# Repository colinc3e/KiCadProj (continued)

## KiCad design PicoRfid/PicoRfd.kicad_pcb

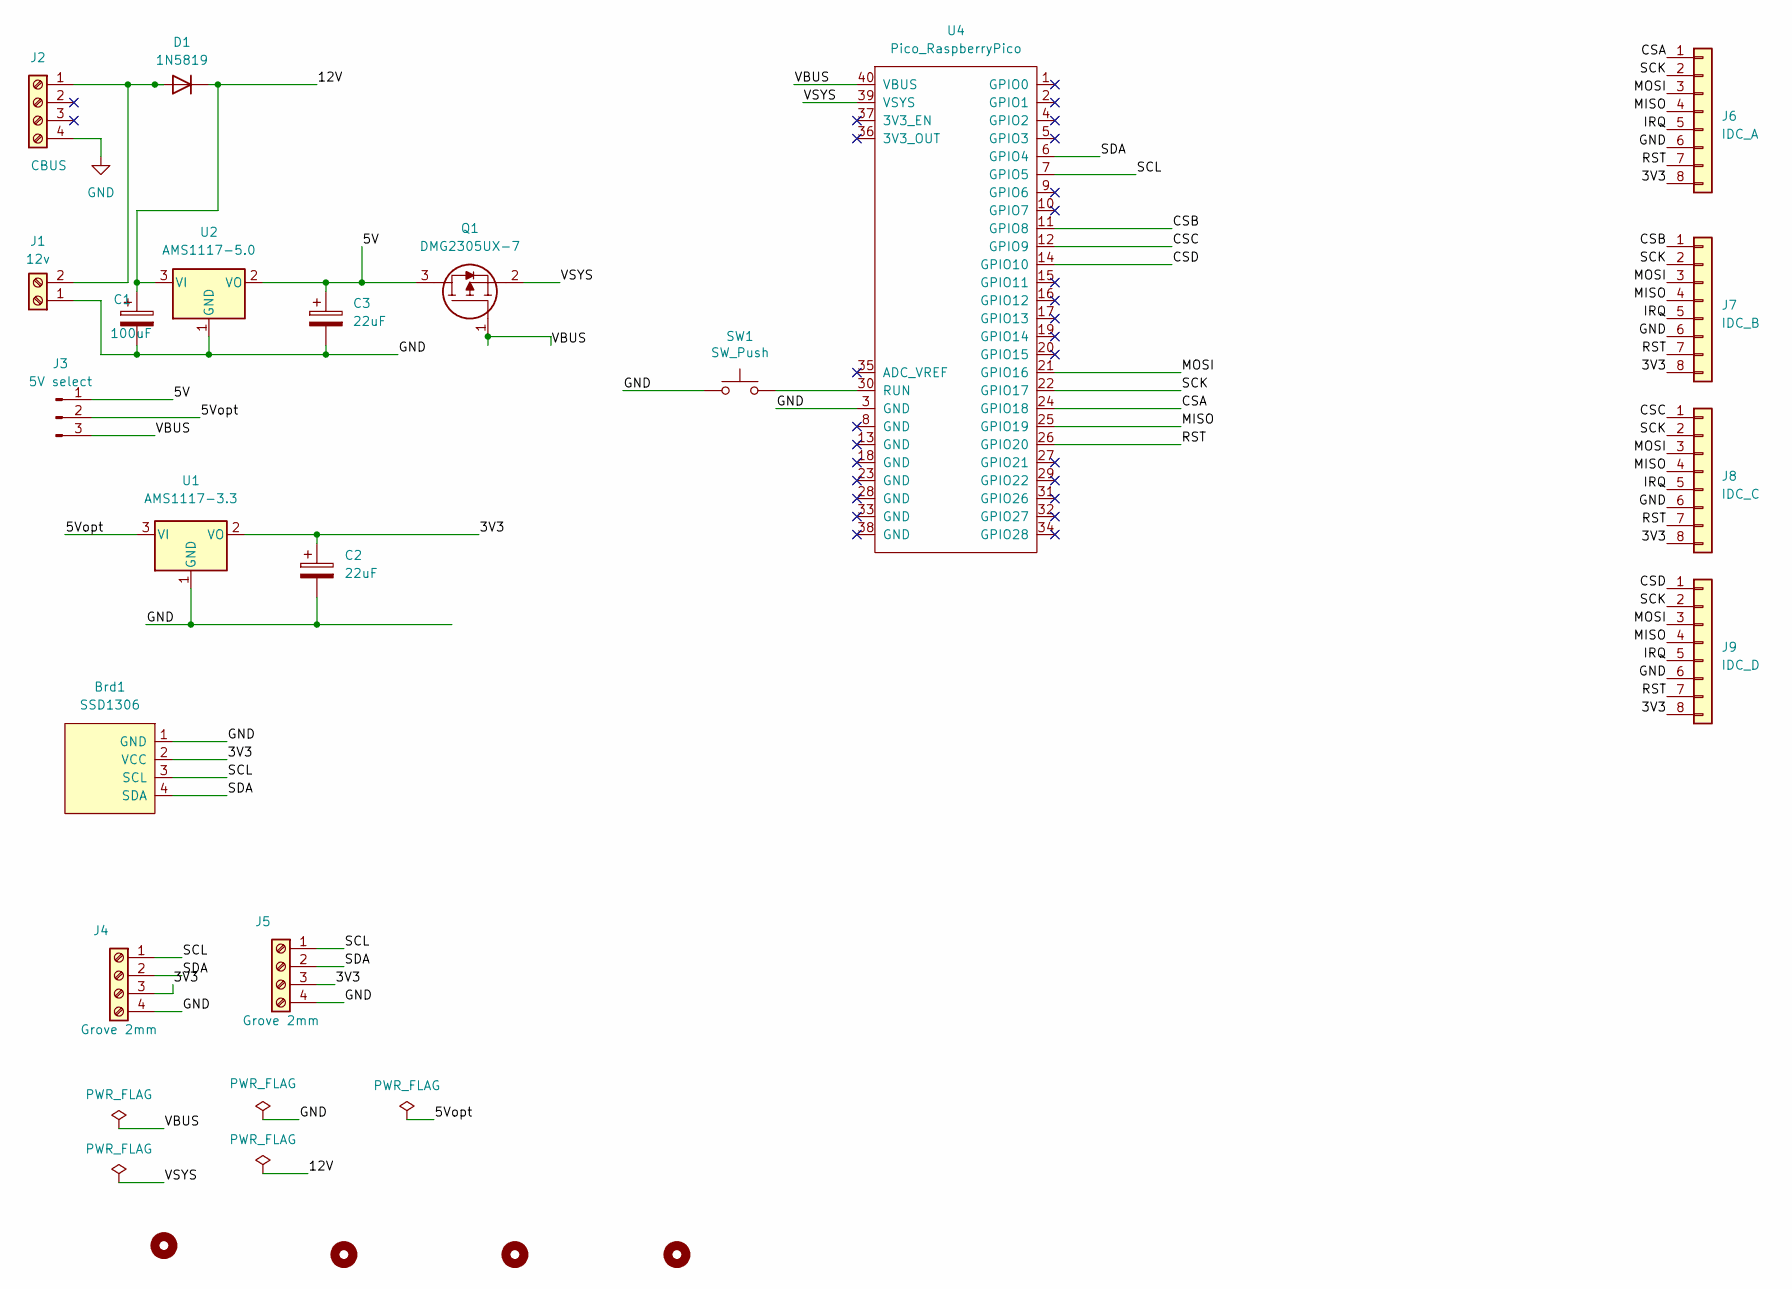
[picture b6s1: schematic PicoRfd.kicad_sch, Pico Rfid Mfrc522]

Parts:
Brd1: SSD1306; 128x64OLED
C1: 100uF; CP_Radial_D10.0mm_P7.50mm
C2, C3: 22uF; CP_Radial_Tantal_D7.0mm_P5.00mm
D1: 1N5819; D_DO-41_SOD81_P10.16mm_Horizontal
H1, H2, H3, H4: MountingHole; MountingHole_3.2mm_M3
J1: 12v; TerminalBlock_Phoenix_PT-1,5-2-3.5-H_1x02_P3.50mm_Horizontal
J2: CBUS; TerminalBlock_Phoenix_PT-1,5-4-3.5-H_1x04_P3.50mm_Horizontal
J3: 5V select; PinHeader_1x03_P2.54mm_Vertical
J4, J5: Grove 2mm; HW4-2.0
J6: IDC_A; IDC-Header_2x04_P2.54mm_Vertical
J7: IDC_B; IDC-Header_2x04_P2.54mm_Vertical
J8: IDC_C; IDC-Header_2x04_P2.54mm_Vertical
J9: IDC_D; IDC-Header_2x04_P2.54mm_Vertical
Q1: DMG2305UX-7; SOT-23-3; Mouser Part Number 621-DMG2305UX-7
SW1: SW_Push; SW_Tactile_SPST_NO_Straight_CK_PTS636Sx25SMTRLFS
U1: AMS1117-3.3; SOT-223-3_TabPin2
U2: AMS1117-5.0; SOT-223-3_TabPin2
U4: Pico_RaspberryPico; RaspberryPico_TH_NoSWD

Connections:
/3V3: Brd1.2 (VCC), C2.1, J4.3, J5.3, J6.8, J7.8, J8.8, J9.8, U1.2 (VO)
/5V: C3.1, J3.1, Q1.3, U2.2 (VO)
/5Vopt: J3.2, U1.3 (VI)
/12V: C1.1, D1.1 (K), U2.3 (VI)
/CSA: J6.1, U4.24 (GPIO18)
/CSB: J7.1, U4.11 (GPIO8)
/CSC: J8.1, U4.12 (GPIO9)
/CSD: J9.1, U4.14 (GPIO10)
/IRQ: J6.5, J7.5, J8.5, J9.5
/MISO: J6.4, J7.4, J8.4, J9.4, U4.25 (GPIO19)
/MOSI: J6.3, J7.3, J8.3, J9.3, U4.21 (GPIO16)
/RST: J6.7, J7.7, J8.7, J9.7, U4.26 (GPIO20)
/SCK: J6.2, J7.2, J8.2, J9.2, U4.22 (GPIO17)
/SCL: Brd1.3 (SCL), J4.1, J5.1, U4.7 (GPIO5)
/SDA: Brd1.4 (SDA), J4.2, J5.2, U4.6 (GPIO4)
/VBUS: J3.3, Q1.1, U4.40 (VBUS)
/VSYS: Q1.2, U4.39 (VSYS)
GND: Brd1.1 (GND), C1.2, C2.2, C3.2, J1.1, J2.4, J4.4, J5.4, J6.6, J7.6, J8.6, J9.6, SW1.1, U1.1 (GND), U2.1 (GND), U4.3 (GND)
unnamed: D1.2 (A), J1.2, J2.1
unnamed: SW1.2, U4.30 (RUN)

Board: 2 copper layers, 23 parts (0 on the bottom side), 20 nets, no tracks yet.

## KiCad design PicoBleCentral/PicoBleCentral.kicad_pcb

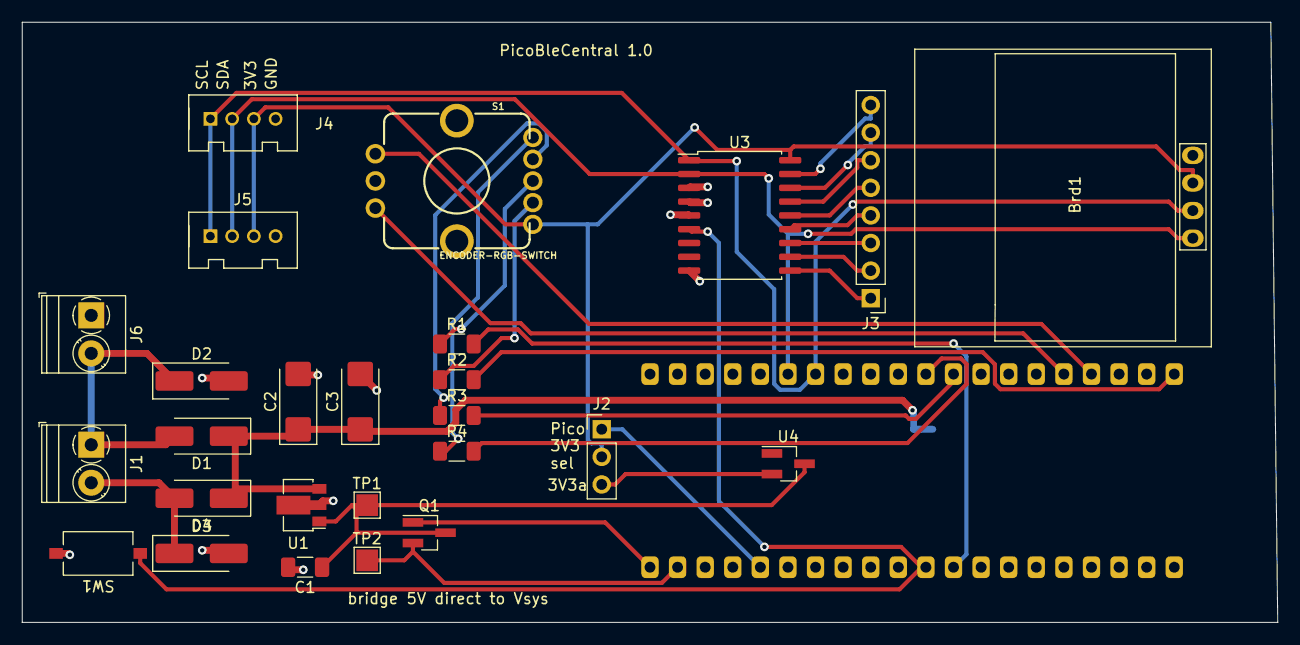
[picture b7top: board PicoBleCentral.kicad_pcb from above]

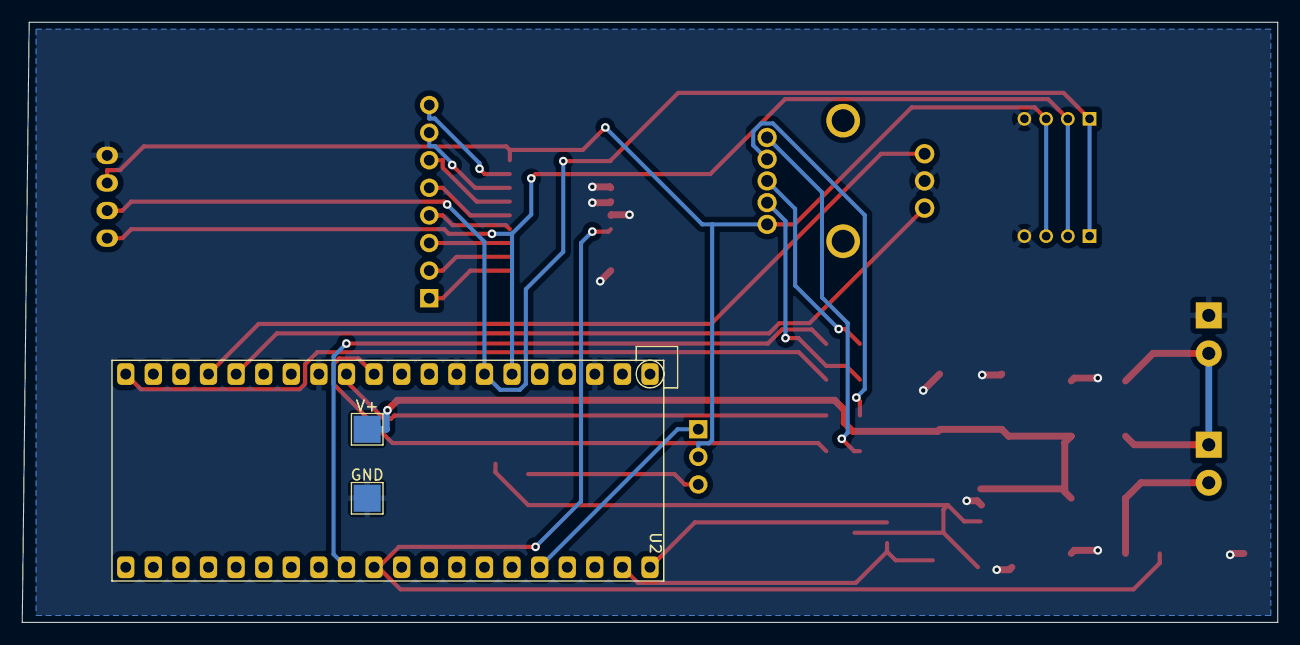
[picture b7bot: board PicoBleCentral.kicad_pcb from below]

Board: 2 copper layers, 115.6 x 55.2 mm, 29 parts (3 on the bottom side), 31 nets.

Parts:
Brd1: SSD1306; 128x64OLED
C1: 10uf/16V; C_1206_3216Metric_Pad1.33x1.80mm_HandSolder
C2: 10uF/25V; CP_EIA-6032-20_AVX-F_Pad2.25x2.35mm_HandSolder
C3: 10uF/25v; CP_EIA-6032-20_AVX-F_Pad2.25x2.35mm_HandSolder
D1, D2, D3, D4: RBR3L60AD; D_SMA_Handsoldering
GND: GND; TestPoint_Pad_2.5x2.5mm
J1: DCC; TerminalBlock_Phoenix_PT-1,5-2-3.5-H_1x02_P3.50mm_Horizontal
J2: 3V3 Sel; PinHeader_1x03_P2.54mm_Vertical
J3: keypad; PinHeader_1x08_P2.54mm_Vertical
J4: grove 2mm; HW4-2.0
J5: i2c; HW4-2.0
J6: 12V; TerminalBlock_Phoenix_PT-1,5-2-3.5-H_1x02_P3.50mm_Horizontal
Q1: DMG2305UX-7; SOT-23_Handsoldering
R1: 10k; R_1206_3216Metric_Pad1.30x1.75mm_HandSolder
R2, R3, R4: 330; R_1206_3216Metric_Pad1.30x1.75mm_HandSolder
S1: ENCODER-RGB-SWITCH; ENCODER_LED_3
SW1: SW_Push; SW_Tactile_SPST_NO_Straight_CK_PTS636Sx25SMTRLFS
TP1, TP2: TestPoint; TestPoint_Pad_2.0x2.0mm
U1: AP7384-50Y; SOT-89-3
U2: Pico_RaspberryPico; RaspberryPico_TH_NoSWD
U3: MCP23008-xSO; SOIC-18W_7.5x11.6mm_P1.27mm
U4: AMS1117-3.3; SOT-23_Handsoldering
V+: +V; TestPoint_Pad_2.5x2.5mm

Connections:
3V3: Brd1.2 (VCC), J2.2, J4.3, J5.3, S1.5 (+), U3.18 (VDD)
3V3_OUT: J2.1, U2.36 (3V3_OUT)
3V3a: J2.3, U4.2 (VO)
+5V: C1.1, Q1.3, TP1.1, U1.1 (VO), U4.3 (VI)
+V: C2.1, C3.1, D1.1 (K), D4.1 (K), U1.3 (VI), V+.1
/DCC1: D1.2 (A), D2.1 (K), J1.1, J6.2
/DCC2: D3.1 (K), D4.2 (A), J1.2
/VSYS: Q1.2, TP2.1, U2.39 (VSYS)
BLUE: R2.2, U2.20 (GPIO15)
BTN: R1.2, U2.29 (GPIO22)
GND: Brd1.1 (GND), C1.2, C2.2, C3.2, D2.2 (A), D3.2 (A), GND.1, J4.4, J5.4, J6.1, S1.C, SW1.2, U1.2 (GND), U2.3 (GND), U2.8 (GND), U2.13 (GND), U3.3 (A2), U3.4 (A1), U3.5 (A0), U3.9 (VSS)
GREEN: R3.2, U2.12 (GPIO9)
unnamed: J3.1, U3.10 (GP0)
unnamed: J3.2, U3.11 (GP1)
unnamed: J3.3, U3.12 (GP2)
unnamed: J3.4, U3.13 (GP3)
unnamed: J3.5, U3.14 (GP4)
unnamed: J3.6, U3.15 (GP5)
unnamed: J3.7, U3.16 (GP6)
unnamed: J3.8, U3.17 (GP7)
unnamed: R2.1, S1.4 (-B)
unnamed: R3.1, S1.2 (-G)
unnamed: R4.1, S1.1 (-R)
unnamed: R1.1, S1.3 (SW)
unnamed: Q1.1, U2.40 (VBUS)
PINA: S1.A, U2.17 (GPIO13)
PINB: S1.B, U2.16 (GPIO12)
RED: R4.2, U2.11 (GPIO8)
RUN: SW1.1, U2.30 (RUN), U3.6 (~RESET)
SCL: Brd1.3 (SCL), J4.1, J5.1, U2.7 (GPIO5), U3.1 (SCL)
SDA: Brd1.4 (SDA), J4.2, J5.2, U2.6 (GPIO4), U3.2 (SDA)

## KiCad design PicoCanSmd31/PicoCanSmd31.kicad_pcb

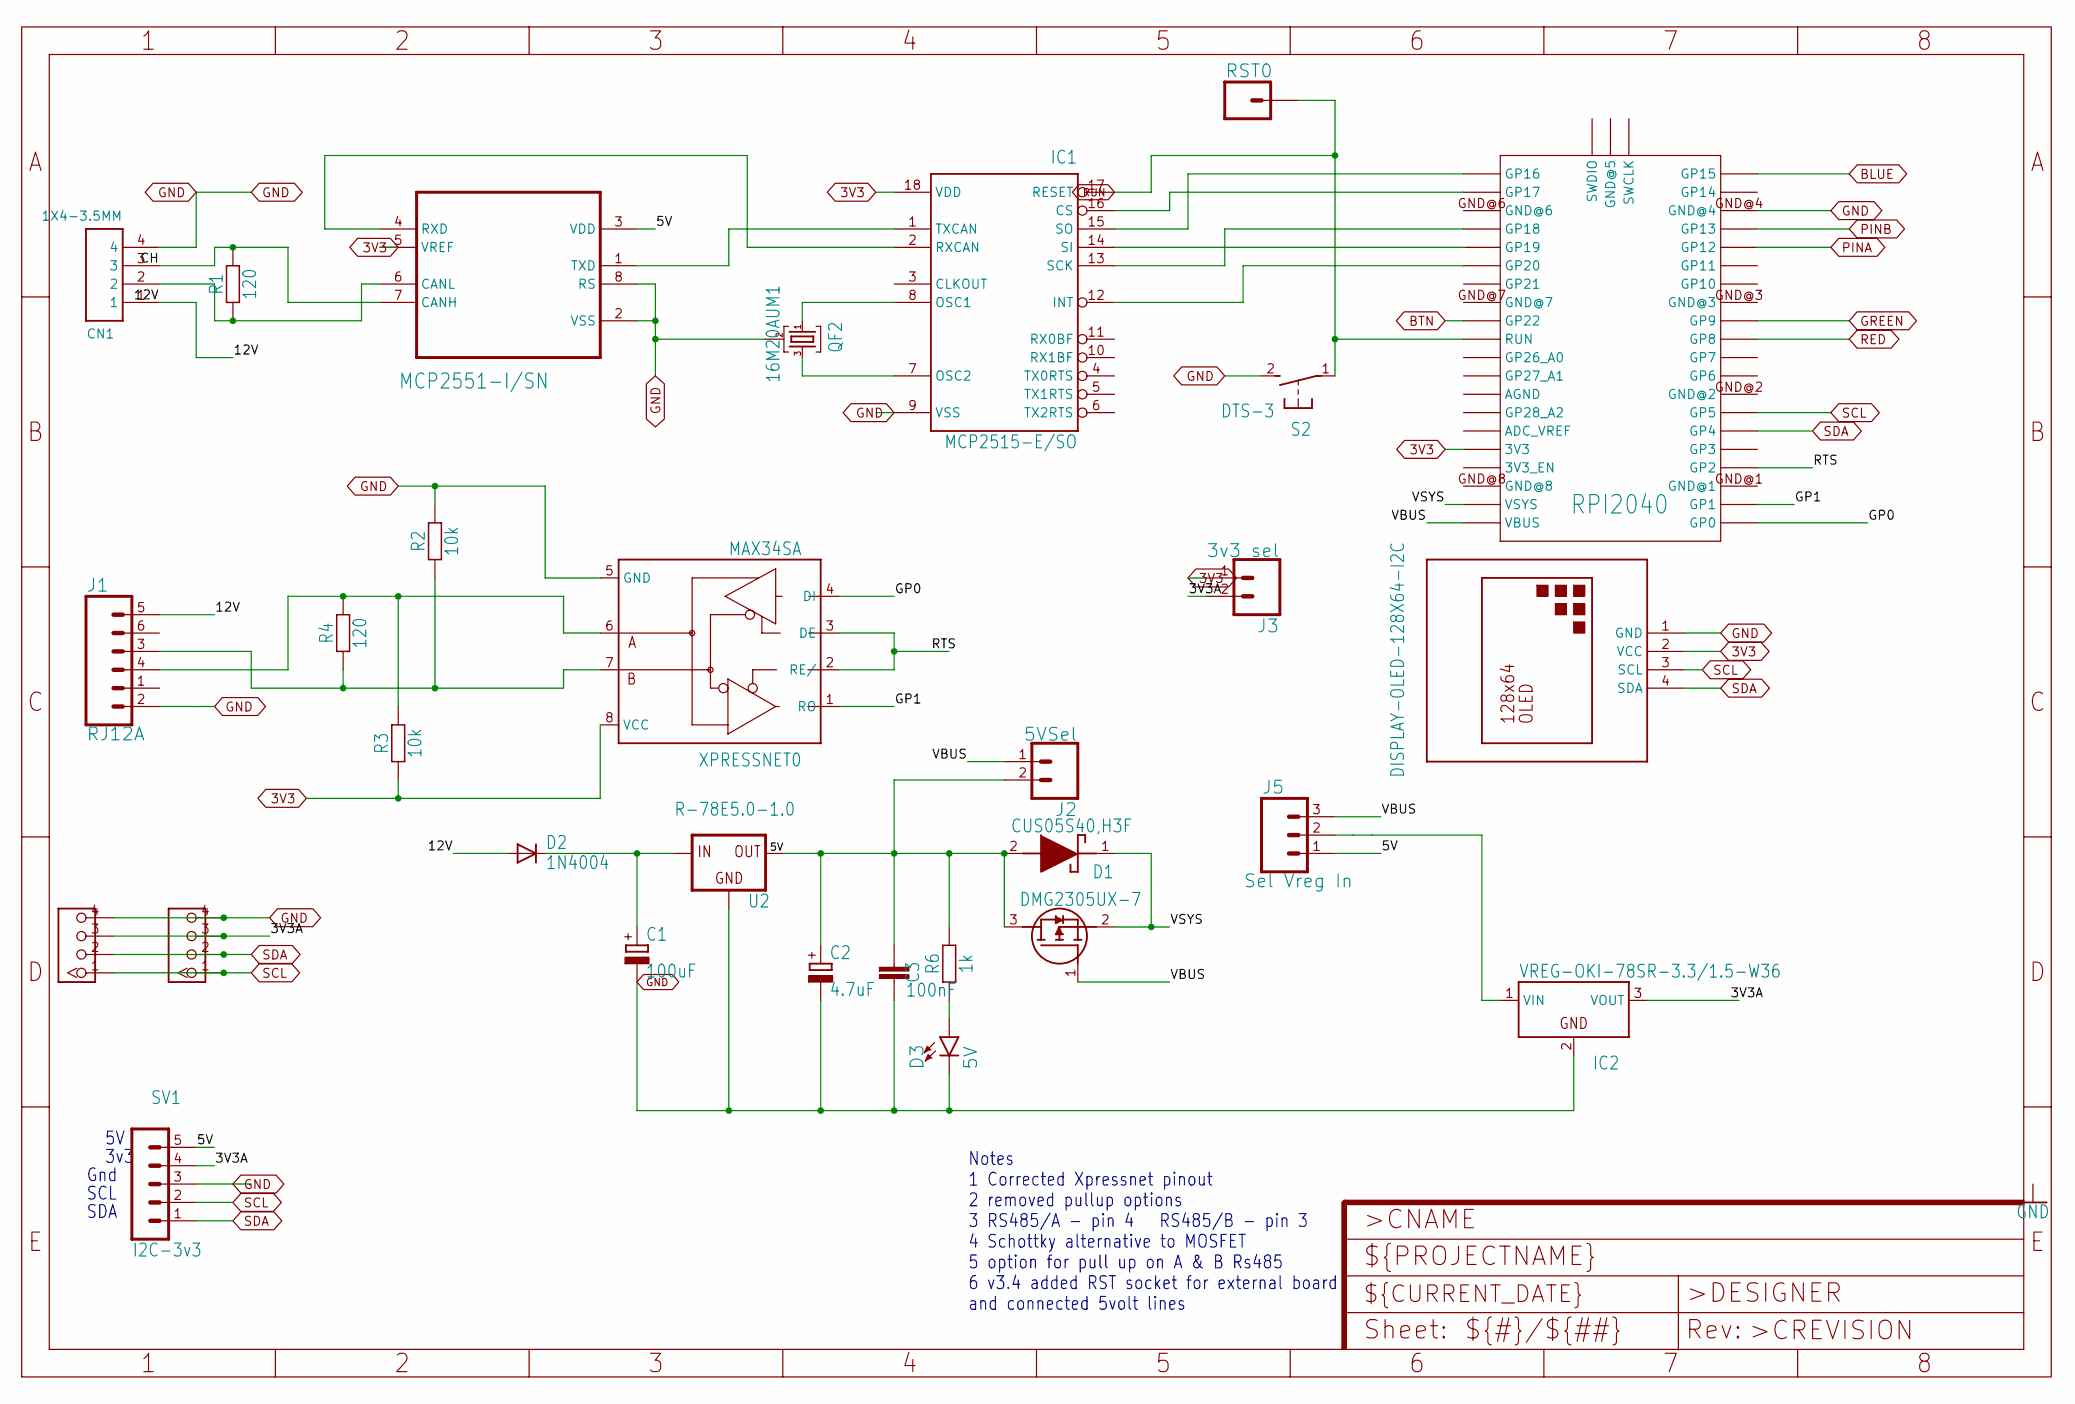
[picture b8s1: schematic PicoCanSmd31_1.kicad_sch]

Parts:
C1: 100uF; E5-8,5
C2: 4.7uF; E5-8,5
C3: 100nF; C025-024X044
CN1: 1X4-3.5MM; 1X04-3.5MM
D1: CUS05S40,H3F; 1SS357TPH3F
D2: 1N4004; DO41-10
D3: 5V; LED_3MM
IC1: MCP2515-E/SO; SO18L
IC2: VREG-OKI-78SR-3.3/1.5-W36; OKI-78SR
J1: RJ12A
J2: 5VSel; 1X02
J3: 3v3 sel; 1X02
J4, J6: 4P-2.0; HW4-2.0
J5: Sel Vreg In; 1X03
Q3: DMG2305UX-7; SOT96P240X110-3N
QF2: 16M20AUM1; UM1
R1, R4: 120; C1206
R2, R3: 10k; C1206
R6: 1k; C1206
RPI2040: RPI_PICO_IG-TH; RPI_PICO_TH
RST0: CONN_01; 1X01
S2: DTS-3
SV1: I2C-3v3; MA05-1
U2: R-78E5.0-1.0; DC-DC_CONVERTER_78XX
U$1: DISPLAY-OLED-128X64-I2C
U$3: MCP2551-I/SN; SOIC127P600X175-8N
XPRESSNET0: MAX34SA; SO08

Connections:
3V3: IC1.18 (VDD), J3.1, R3.1, RPI2040.3V3, U$1.2 (VCC), U$3.5 (VREF), XPRESSNET0.8 (VCC); also elsewhere on the board
3V3A: IC2.3 (VOUT), J3.2, J4.3, J6.3, SV1.4
5V: C2.+, C3.1, D1.2 (A), J2.2, J5.1, Q3.3 (D), R6.2, SV1.5, U2.VOUT (OUT), U$3.3 (VDD)
12V: CN1.1, D2.A, J1.5
BLUE: RPI2040.GP15; also elsewhere on the board
BTN: RPI2040.GP22; also elsewhere on the board
CH: CN1.3, R1.2, U$3.7 (CANH)
CL: CN1.2, R1.1, U$3.6 (CANL)
GND: C1.-, C2.-, C3.2, CN1.4, D3.K (C), IC1.9 (VSS), IC2.2 (GND), J1.2 (1), J4.4, J6.4, QF2.2, R2.2, RPI2040.GND@4, S2.2, SV1.3, U2.GND, U$1.1 (GND), U$3.2 (VSS), U$3.8 (RS), XPRESSNET0.5 (GND); also elsewhere on the board
GP0: RPI2040.GP0, XPRESSNET0.4 (DI)
GP1: RPI2040.GP1, XPRESSNET0.1 (RO)
GREEN: RPI2040.GP9; also elsewhere on the board
unnamed: J1.4 (3), R3.2, R4.2, XPRESSNET0.6 (A)
unnamed: J1.3 (4), R2.1, R4.1, XPRESSNET0.7 (B)
unnamed: IC1.1 (TXCAN), U$3.1 (TXD)
unnamed: IC1.2 (RXCAN), U$3.4 (RXD)
unnamed: IC1.8 (OSC1), QF2.1
unnamed: IC1.7 (OSC2), QF2.3
unnamed: IC1.16 (CS), RPI2040.GP17
unnamed: IC1.15 (SO), RPI2040.GP16
unnamed: IC1.14 (SI), RPI2040.GP19
unnamed: IC1.13 (SCK), RPI2040.GP18
unnamed: IC1.12 (INT), RPI2040.GP20
unnamed: IC2.1 (VIN), J5.2
unnamed: C1.+, D2.C, U2.VIN (IN)
unnamed: D3.A, R6.1
PINA: RPI2040.GP12; also elsewhere on the board
PINB: RPI2040.GP13; also elsewhere on the board
RED: RPI2040.GP8; also elsewhere on the board
RTS: RPI2040.GP2, XPRESSNET0.2 (RE/), XPRESSNET0.3 (DE)
RUN: IC1.17 (RESET), RPI2040.RUN, RST0.1, S2.1; also elsewhere on the board
SCL: J4.1, J6.1, RPI2040.GP5, SV1.2, U$1.3 (SCL); also elsewhere on the board
SDA: J4.2, J6.2, RPI2040.GP4, SV1.1, U$1.4 (SDA); also elsewhere on the board
VBUS: J2.1, J5.3, Q3.1 (G), RPI2040.VBUS
VSYS: D1.1 (K), Q3.2 (S), RPI2040.VSYS

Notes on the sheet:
SCL
Gnd
Notes 1 Corrected Xpressnet pinout 2 removed pullup options 3 RS485/A - pin 4 RS485/B - pin 3 4 Schottky alternative to MOSFET 5 option for pull up on A & B Rs485 6 v3.4 added RST socket for external board and connected 5volt lines
3v3
SDA

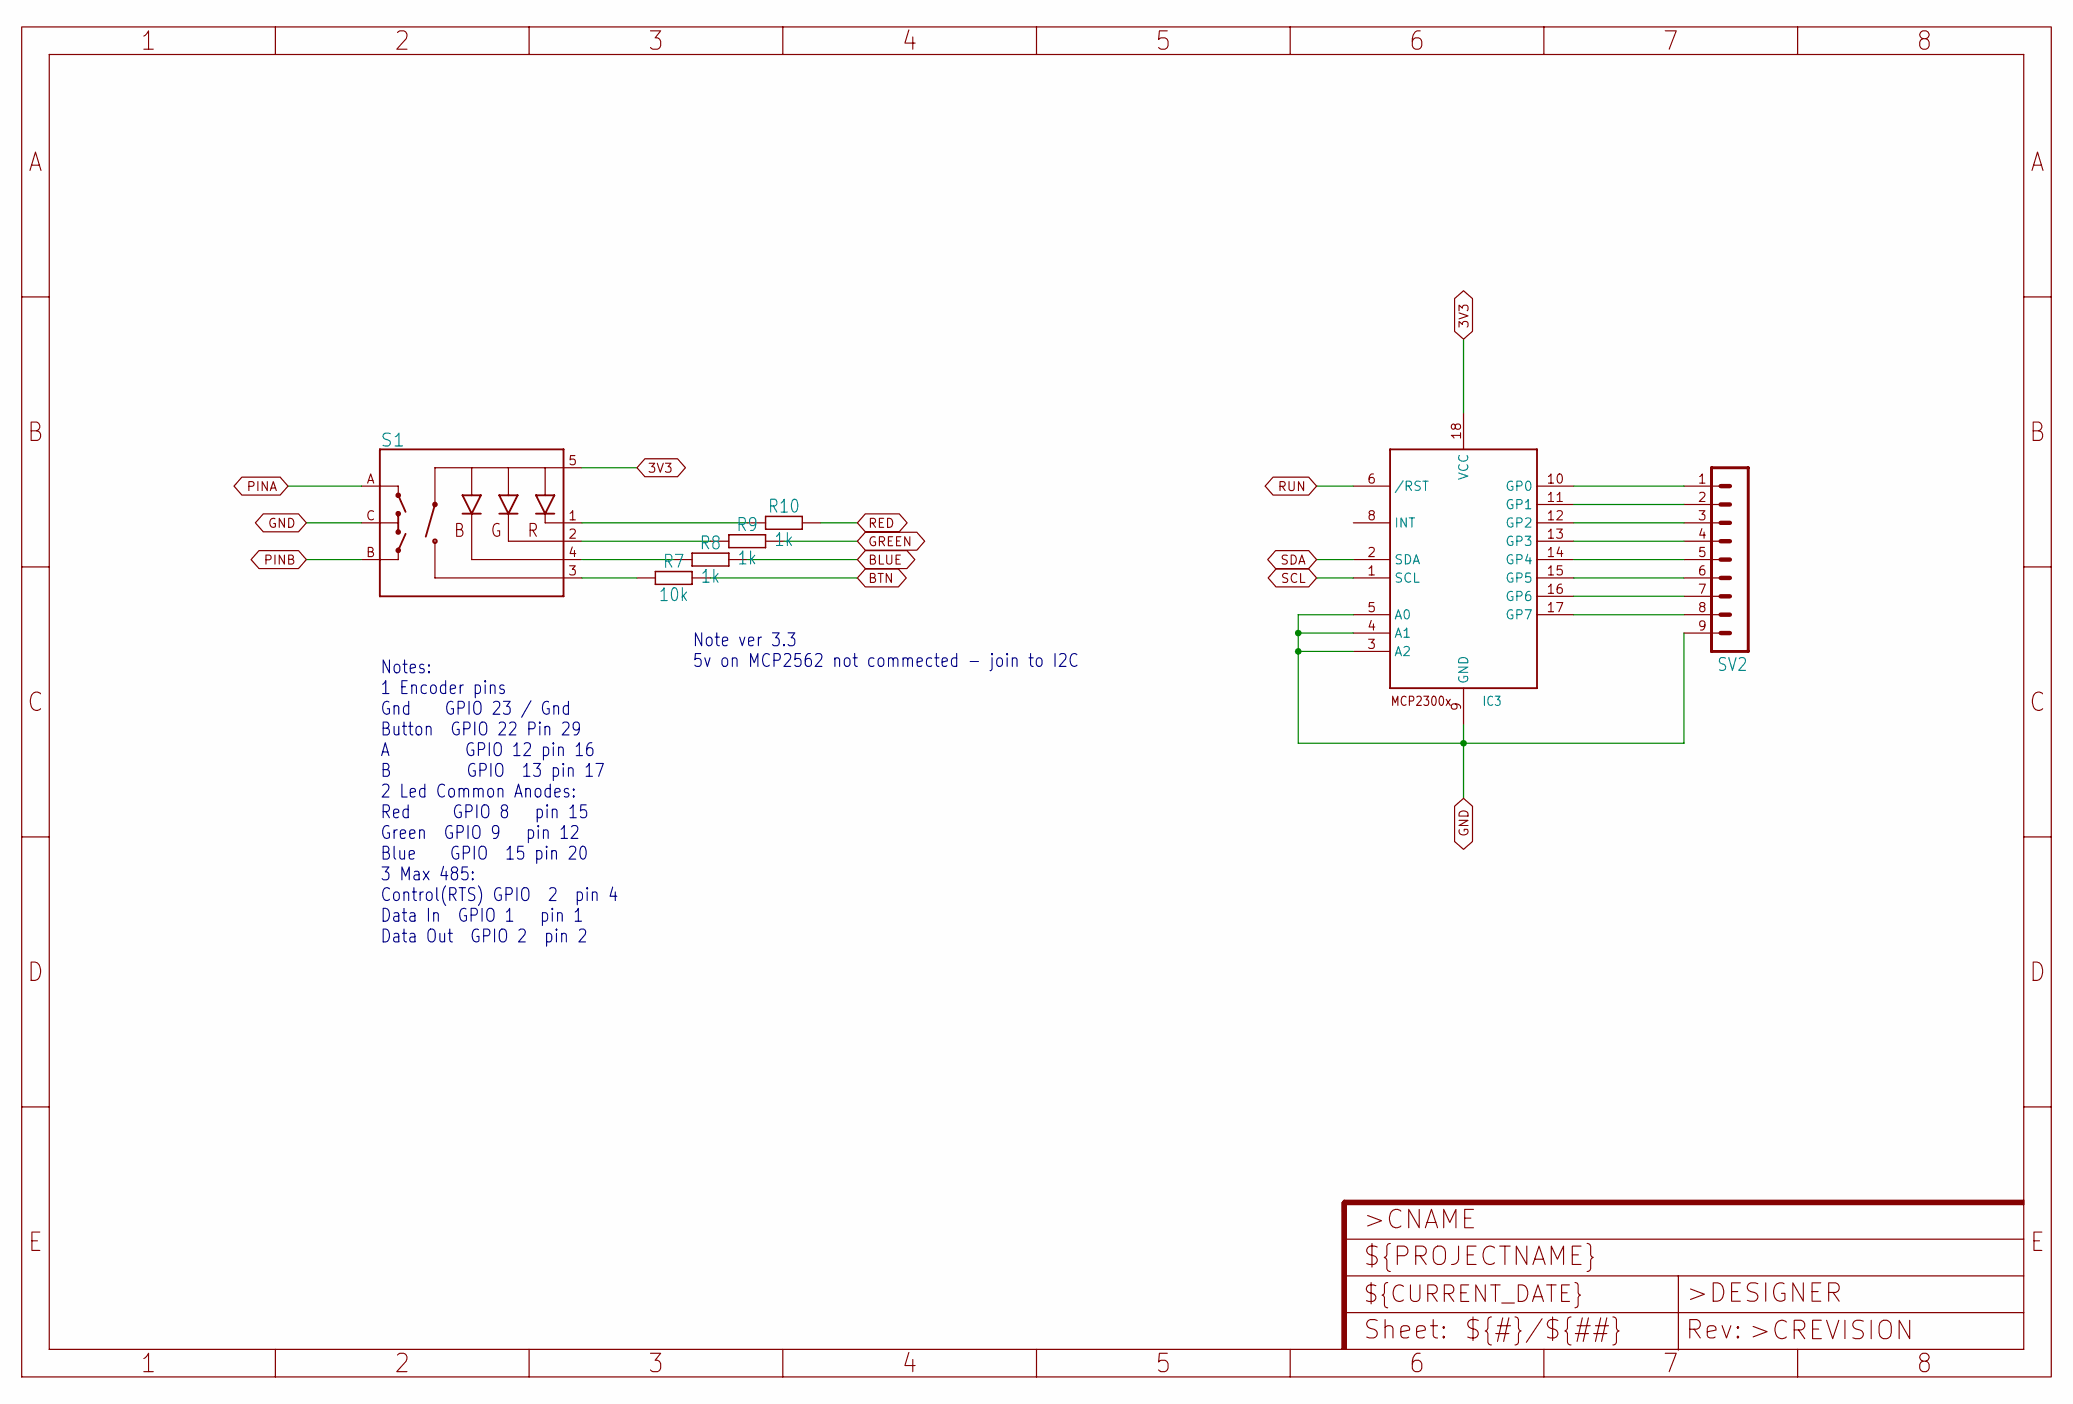
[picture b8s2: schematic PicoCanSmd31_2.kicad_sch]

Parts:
IC3: MCP23008/SO; SO18W
R7: 10k; C1206
R8, R9, R10: 1k; C1206
S1: ENCODER-RGB-SWITCH; ENCODER_LED_3
SV2: MA09-1

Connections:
3V3: IC3.18 (VCC), S1.5 (+); also elsewhere on the board
BLUE: R8.2; also elsewhere on the board
BTN: R7.2; also elsewhere on the board
GND: IC3.3 (A2), IC3.4 (A1), IC3.5 (A0), IC3.9 (GND), S1.C, SV2.9; also elsewhere on the board
GREEN: R9.2; also elsewhere on the board
unnamed: R8.1, S1.4 (-B)
unnamed: R9.1, S1.2 (-G)
unnamed: R10.1, S1.1 (-R)
unnamed: IC3.10 (GP0), SV2.1
unnamed: R7.1, S1.3 (SW)
unnamed: IC3.11 (GP1), SV2.2
unnamed: IC3.12 (GP2), SV2.3
unnamed: IC3.13 (GP3), SV2.4
unnamed: IC3.14 (GP4), SV2.5
unnamed: IC3.15 (GP5), SV2.6
unnamed: IC3.16 (GP6), SV2.7
unnamed: IC3.17 (GP7), SV2.8
PINA: S1.A; also elsewhere on the board
PINB: S1.B; also elsewhere on the board
RED: R10.2; also elsewhere on the board
RUN: IC3.6 (/RST); also elsewhere on the board
SCL: IC3.1 (SCL); also elsewhere on the board
SDA: IC3.2 (SDA); also elsewhere on the board

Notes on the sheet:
Notes: 1 Encoder pins Gnd GPIO 23 / Gnd Button GPIO 22 Pin 29 A GPIO 12 pin 16 B GPIO 13 pin 17 2 Led Common Anodes: Red GPIO 8 pin 15 Green GPIO 9 pin 12 Blue GPIO 15 pin 20 3 Max 485: Control(RTS) GPIO 2 pin 4 Data In GPIO 1 pin 1 Data Out GPIO 2 pin 2
Note ver 3.3 5v on MCP2562 not commected - join to I2C

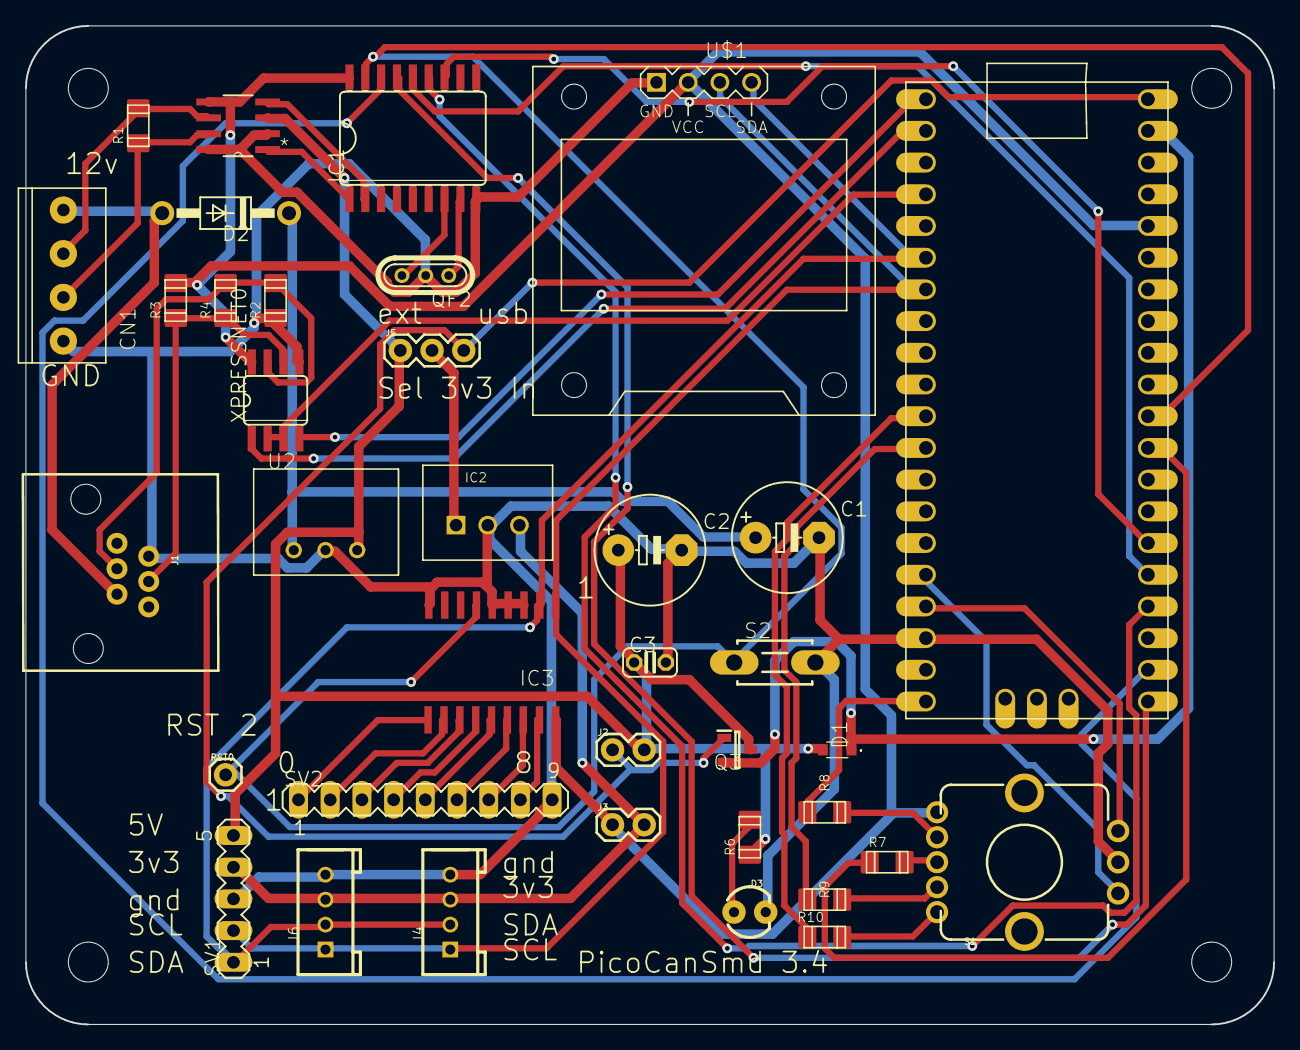
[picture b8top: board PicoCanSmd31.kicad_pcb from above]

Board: 2 copper layers, 100.0 x 80.0 mm, 41 parts (0 on the bottom side), 47 nets.

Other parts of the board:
@HOLE0, @HOLE1, @HOLE2, @HOLE3: (no value)

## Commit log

2024-04-09 11:29 Arrakis.local
2024-04-10 12:08 Arrakis.local
2024-04-10 13:19 Arrakis.local
2024-04-10 19:27 Arrakis.local
2024-04-11 12:28 Arrakis.local
2024-04-11 21:55 Arrakis.local
2024-04-11 09:25 Arrakis.local
2024-04-12 13:10 Arrakis.local
2024-04-12 19:39 Arrakis.local
2024-04-12 20:43 Titan.local
2024-04-12 20:47 Titan.local
2024-04-12 21:25 Titan.local
2024-04-14 10:23 Arrakis.local
2024-04-15 14:57 Arrakis.local
2024-04-15 08:20 Arrakis.local
2024-04-15 08:27 Arrakis.local
2024-04-16 12:56 Arrakis.local
2024-04-16 12:56 Titan.local
2024-04-18 18:34 Arrakis.local
2024-04-20 20:02 Arrakis.local
2024-05-25 09:48 Titan.local
2024-05-26 15:58 Arrakis.local
2024-06-03 19:58 Titan.local
2024-06-04 20:18 Arrakis.local
2024-06-04 10:15 Arrakis.local
2024-06-07 20:04 Titan.local
2024-06-29 20:53 Arrakis.local
2024-06-29 22:27 Titan.local
2024-07-01 08:44 Titan.local
2024-07-09 16:37 Titan.local
2024-07-09 08:55 Titan.local
2024-07-16 14:40 Arrakis.local
2024-07-17 20:06 Arrakis.local
2024-07-26 09:23 Titan.local
2024-08-02 21:22 Arrakis.local
2024-08-02 21:44 Titan.local
2024-08-03 20:38 Arrakis.local
2024-08-03 21:37 Titan.local
2024-08-29 11:44 Titan.local
2024-10-20 11:39 Titan.local
2024-10-20 12:25 Titan.local
2024-10-21 22:30 Titan.local
2024-10-22 14:17 Titan.local
2024-10-22 14:29 Titan.local
2024-10-22 14:30 Arrakis.local
2024-10-22 14:39 Arrakis.local
2024-10-22 15:42 Titan.local
2024-10-22 16:42 Titan.local
2024-10-22 18:01 Arrakis.local
2024-10-22 21:35 Arrakis.local
2024-10-22 22:53 Titan.local
2024-10-23 16:26 Titan.local
2024-10-23 16:43 Titan.local
2024-10-23 17:14 Arrakis.local
2024-10-23 17:48 Arrakis.local
2024-10-23 20:04 Arrakis.local
2024-10-23 20:57 Titan.local
2024-10-23 21:39 Arrakis.local
2024-10-24 14:34 Titan.local
2024-10-24 16:27 Arrakis.local
2024-10-24 16:27 Titan.local
2024-10-24 16:59 Titan.local
2024-10-24 17:05 Titan.local
2024-10-24 08:19 Titan.local
2024-10-24 09:08 Titan.local
2024-10-24 09:35 Titan.local
2024-10-25 22:14 Arrakis.local
2024-10-25 11:31 Titan.local
2024-10-28 14:23 Arrakis.local
2024-10-28 14:24 Titan.local
2024-10-28 14:47 Arrakis.local
2024-10-28 14:53 Arrakis.local
2024-10-28 15:03 Titan.local
2024-10-28 16:04 Arrakis.local
2024-10-28 +%d/%m/%y 09:55 Arrakis.local
2024-10-28 ' +%d/%m/%y' 09:57 Arrakis.local
2024-10-28 date '+%d/%m/%y' 11:46 Titan.local
2024-10-28 '+%d/%m/%y' 11:49 Titan.local
2024-10-28 29/10/24 11:54 Titan.local
2024-11-06 06/11/24 18:34 Arrakis.local
2024-11-06 06/11/24 19:09 Arrakis.local
2024-11-28 29/11/24 11:14 Arrakis.local
2024-11-30 30/11/24 17:42 Arrakis.local
2024-11-30 30/11/24 19:40 Titan.local
2024-11-30 30/11/24 22:26 Arrakis.local
2024-11-30 01/12/24 09:58 Titan.local
2024-11-30 01/12/24 11:15 Titan.local
2024-12-01 01/12/24 13:50 Arrakis.local
2024-12-01 01/12/24 14:03 Titan.local
2024-12-01 01/12/24 14:49 Titan.local
2024-12-01 01/12/24 16:56 Titan.local
2024-12-01 01/12/24 17:12 Titan.local
2024-12-01 01/12/24 17:50 Arrakis.local
2024-12-01 01/12/24 18:25 Titan.local
2024-12-01 01/12/24 22:40 Titan.local
2024-12-01 02/12/24 08:43 Titan.local
2024-12-01 02/12/24 10:42 Arrakis.local
2024-12-01 02/12/24 11:29 Titan.local
2024-12-03 03/12/24 20:50 Titan.local
2024-12-03 03/12/24 21:06 Titan.local
2024-12-03 03/12/24 21:34 Arrakis.local
2024-12-03 03/12/24 21:55 Titan.local
2024-12-03 03/12/24 22:49 Titan.local
2024-12-03 04/12/24 09:57 Arrakis.local
2024-12-04 04/12/24 19:40 Titan.local
2024-12-04 04/12/24 19:52 Titan.local
2024-12-04 04/12/24 20:52 Arrakis.local
2024-12-04 04/12/24 21:07 Titan.local
2024-12-04 04/12/24 21:29 Arrakis.local
2024-12-04 04/12/24 22:17 Titan.local
2024-12-04 05/12/24 09:43 Titan.local
2024-12-04 05/12/24 09:47 Arrakis.local
2024-12-04 05/12/24 10:04 Titan.local
2024-12-04 05/12/24 10:29 Titan.local
2024-12-09 09/12/24 16:37 Arrakis.local
2024-12-09 09/12/24 16:51 Arrakis.local
2024-12-09 09/12/24 17:09 Arrakis.local
2024-12-09 09/12/24 22:16 Arrakis.local
2024-12-09 09/12/24 22:33 Titan.local
2024-12-10 10/12/24 16:11 Arrakis.local
2024-12-28 28/12/24 16:08 Titan.local
2024-12-28 28/12/24 16:20 Titan.local
2025-01-10 10/01/25 20:22 Titan.local
2025-01-18 18/01/25 20:46 Arrakis.local
2025-01-18 18/01/25 22:46 Titan.local
2025-01-19 19/01/25 19:37 Arrakis.local
2025-01-19 19/01/25 21:01 Arrakis.local
2025-01-19 19/01/25 21:02 Arrakis.local
2025-01-19 19/01/25 22:12 Titan.local
2025-01-20 20/01/25 13:14 Arrakis.local
2025-01-20 20/01/25 13:46 Titan.local
2025-01-20 20/01/25 19:41 Arrakis.local
2025-01-20 20/01/25 20:01 Titan.local
2025-01-20 20/01/25 21:17 Titan.local
2025-01-20 20/01/25 21:36 Titan.local
2025-01-20 20/01/25 21:44 Titan.local
2025-01-20 20/01/25 21:53 Arrakis.local
2025-01-20 20/01/25 22:19 Titan.local
2025-01-20 21/01/25 09:06 Titan.local
2025-01-20 21/01/25 09:15 Arrakis.local
2025-01-21 21/01/25 15:35 Arrakis.local
2025-01-21 21/01/25 16:03 Arrakis.local
2025-01-21 21/01/25 18:52 Arrakis.local
2025-04-28 29/04/25 07:43 Arrakis.local
2025-05-10 11/05/25 09:47 Arrakis.local
2025-05-10 11/05/25 10:37 Arrakis.local
2025-05-10 11/05/25 10:39 Arrakis.local
2025-05-11 11/05/25 20:19 Arrakis.local
2025-05-12 12/05/25 16:59 Arrakis.local
2025-05-12 12/05/25 20:40 Arrakis.local
2025-05-12 12/05/25 20:56 Arrakis.local
2025-05-12 12/05/25 21:51 Titan.local
2025-05-12 12/05/25 21:56 Arrakis.local
2025-05-15 16/05/25 09:45 Arrakis.local
2025-05-20 20/05/25 20:56 Arrakis.local
2025-05-23 23/05/25 17:16 Arrakis.local
2025-05-23 23/05/25 17:17 Titan.local
2025-05-26 26/05/25 19:16 Arrakis.local
2025-05-26 26/05/25 20:18 Titan.local
2025-05-26 26/05/25 20:40 Titan.local
2025-05-26 26/05/25 22:33 Titan.local
2025-05-26 27/05/25 08:45 Arrakis.local
2025-05-26 27/05/25 09:08 Arrakis.local
2025-05-26 27/05/25 10:06 Arrakis.local
2025-05-27 27/05/25 12:17 Titan.local
2025-05-28 28/05/25 13:45 Arrakis.local
2025-05-28 28/05/25 15:48 Arrakis.local
2025-05-29 30/05/25 09:30 Arrakis.local
2025-09-06 06/09/25 21:49 Titan.local
2025-09-06 06/09/25 22:34 Titan.local
2025-09-06 06/09/25 22:44 Arrakis.local
2025-09-06 07/09/25 10:05 Arrakis.local
2025-09-06 07/09/25 10:39 Titan.local
2025-09-06 07/09/25 11:15 Arrakis.local
2025-09-07 07/09/25 16:49 Arrakis.local
2025-09-07 07/09/25 17:28 Titan.local
2025-09-07 07/09/25 17:46 Titan.local
2025-09-07 07/09/25 17:52 Arrakis.local
2025-09-07 07/09/25 21:50 Titan.local
2025-09-07 07/09/25 22:02 Titan.local
2025-09-07 07/09/25 22:20 Titan.local
2025-09-07 08/09/25 08:22 Arrakis.local
2025-09-07 08/09/25 08:45 Titan.local
2025-09-07 08/09/25 09:04 Arrakis.local
2025-09-08 08/09/25 13:36 Titan.local
2025-09-08 08/09/25 14:33 Titan.local
2025-09-08 08/09/25 19:49 Arrakis.local
2025-09-08 08/09/25 20:07 Titan.local
2025-09-08 08/09/25 21:54 Titan.local
2025-09-08 09/09/25 09:18 Arrakis.local
2025-09-08 09/09/25 10:15 Titan.local
2025-09-08 09/09/25 11:50 Arrakis.local
2025-09-09 09/09/25 12:23 Arrakis.local
2025-09-09 09/09/25 14:27 Titan.local
2025-09-09 09/09/25 14:42 Arrakis.local
2025-09-09 09/09/25 16:21 Titan.local
2025-09-09 10/09/25 07:25 Titan.local
2025-09-09 10/09/25 10:03 Titan.local
2025-09-10 10/09/25 12:32 Titan.local
2025-09-10 10/09/25 13:02 Titan.local
2025-09-10 10/09/25 15:44 Arrakis.local
2025-09-10 10/09/25 15:44 Titan.local
2025-09-12 12/09/25 15:24 Titan.local
2025-09-12 13/09/25 09:47 Arrakis.local
2025-09-13 13/09/25 20:26 Titan.local
2025-09-14 14/09/25 14:58 Arrakis.local
2025-09-14 14/09/25 15:04 Titan.local
2025-09-14 14/09/25 16:21 Arrakis.local
